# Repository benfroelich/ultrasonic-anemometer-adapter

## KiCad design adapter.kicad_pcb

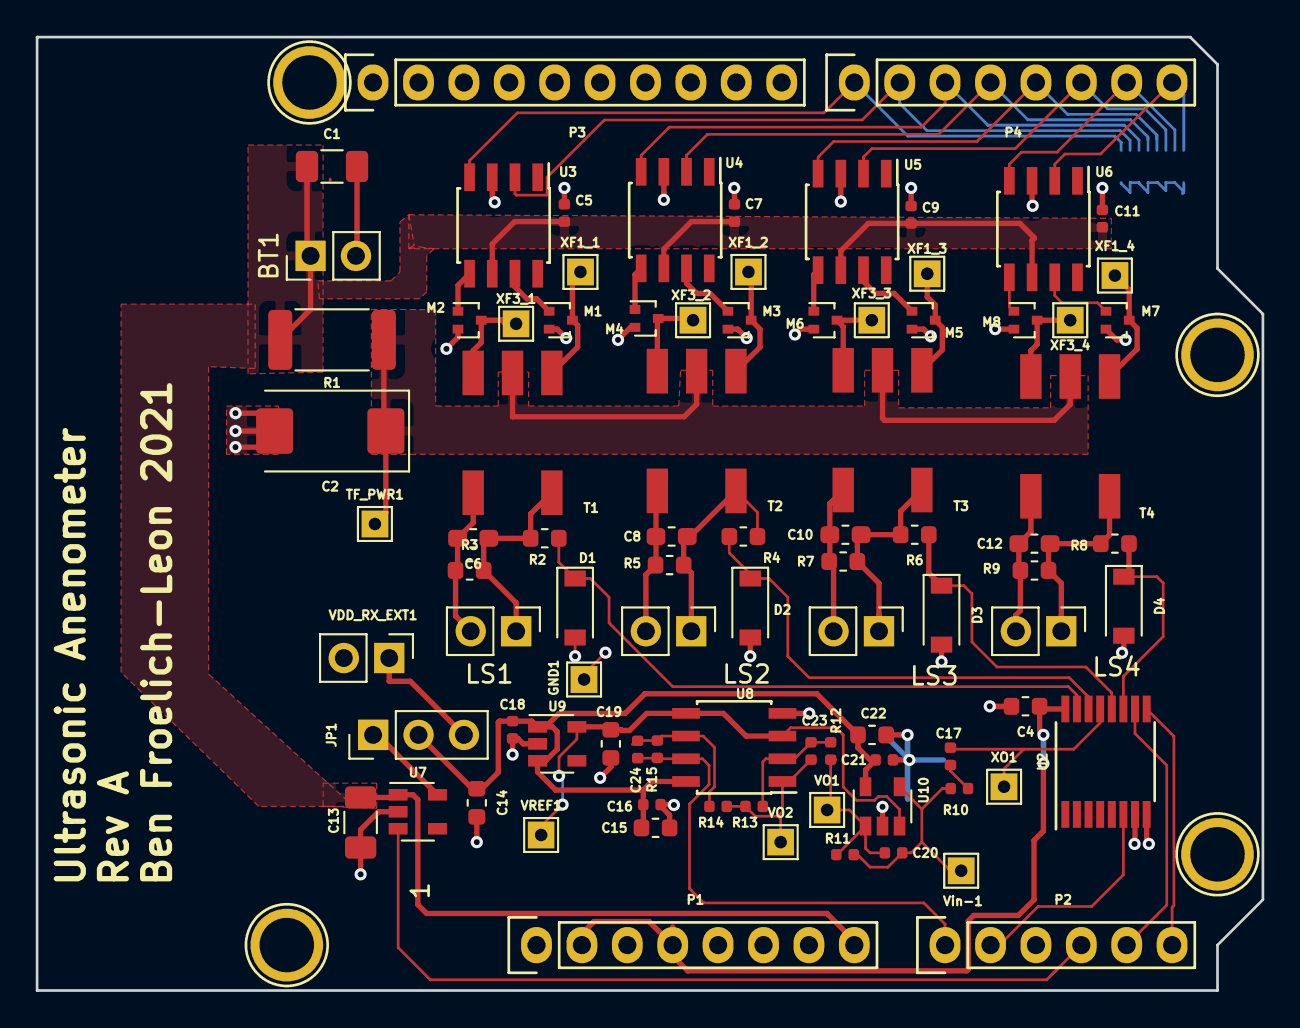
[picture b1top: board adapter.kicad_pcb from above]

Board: 2 copper layers, 68.6 x 53.3 mm, 94 parts (1 on the bottom side), 52 nets.

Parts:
BT1: 9 V; PinHeader_1x02_P2.54mm_Vertical_TE-Connectivity-640456-2‎
C1, C13: 4.7uF; C_1206_3216Metric
C2: 100uF; CP_EIA-7343-31_Kemet-D
C4: 4.7 uF; C_0603_1608Metric
C5, C7, C9, C11, C16, C18, C21: 100nF; C_0402_1005Metric
C6, C8, C10, C12: 1500p; C_0603_1608Metric_Pad1.05x0.95mm_HandSolder
C14, C15, C19, C22: 4.7uF; C_0603_1608Metric
C17: 100n; C_0402_1005Metric
C20, C23, C24: 1pF; C_0402_1005Metric
D1, D2, D3, D4: DDZ9678-7; D_SOD-123
GND1: TEST_1P; TestPoint_THTPad_1.5x1.5mm_Drill0.7mm
JP1: Jumper_3_Bridged12; PinHeader_1x03_P2.54mm_Vertical
LS1, LS2, LS3, LS4: Speaker_Ultrasound; PinHeader_1x02_P2.54mm_Vertical_TE-Connectivity-640456-2‎
M1, M2, M3, M4, M5, M6, M7, M8: PJE138K; SOT-416
P1: Power; Socket_Strip_Arduino_1x08
P2: Analog; Socket_Strip_Arduino_1x06
P3: Digital; Socket_Strip_Arduino_1x10
P4: Digital; Socket_Strip_Arduino_1x08
P5, P6, P7, P8: CONN_01X01; Arduino_1pin
R1: 100; R_2512_6332Metric
R2, R4, R6, R8: 10k; R_0603_1608Metric
R3, R5, R7, R9: 1.8k; R_0603_1608Metric
R10: 2.2k; R_0402_1005Metric
R11: 10k; R_0402_1005Metric
R12, R14: 4.3k; R_0402_1005Metric
R13, R15: 43k; R_0402_1005Metric
RN1: 100k; R_Array_Convex_8x0602
T1, T2, T3, T4: Transformer_SP_1S; B78416
TF_PWR1: TEST_1P; TestPoint_THTPad_1.5x1.5mm_Drill0.7mm
U2: SN74LV4052; TSSOP-16_4.4x5mm_P0.65mm
U3, U4, U5, U6: TC4427AVOA; SOIC-8_3.9x4.9mm_P1.27mm
U7: TPS76933; SOT-23-5
U8: OPA2322AID; SOIC-8_3.9x4.9mm_P1.27mm
U9: TLV70215_SOT23-5; SOT-23-5
U10: LMP7731MFE; SOT-23-5
VDD_RX_EXT1: TEST; PinHeader_1x02_P2.54mm_Vertical
VO1, VO2: TEST_1P; TestPoint_THTPad_1.5x1.5mm_Drill0.7mm
VREF1: TEST_1P; TestPoint_THTPad_1.5x1.5mm_Drill0.7mm
Vin-1: TEST_1P; TestPoint_THTPad_1.5x1.5mm_Drill0.7mm
XF1_1, XF1_2, XF1_3, XF1_4, XF3_1, XF3_2, XF3_3, XF3_4: TEST_1P; TestPoint_THTPad_1.5x1.5mm_Drill0.7mm
XO1: TEST_1P; TestPoint_THTPad_1.5x1.5mm_Drill0.7mm

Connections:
+3V3: C4.1, P1.2, P1.4, U2.16
+9V: BT1.1, C1.1, C5.1, C7.1, C9.1, C11.1, C13.1, P1.8, R1.2, U3.6, U4.6, U5.6, U6.6, U7.1
/PA0: C24.1, P2.1, R15.1, U8.7
/PA1: P2.2, U2.6
/PA2: P4.7, RN1.15, U6.4
/PA3: P4.8, RN1.16, U6.2
/PA8: P4.1, RN1.9, U3.4
/PA10: P4.6, RN1.14, U5.2
/PB0: P2.4, U7.3
/PB3: P4.5, RN1.13, U5.4
/PB4: P4.3, RN1.11, U4.4
/PB5: P4.4, RN1.12, U4.2
/PB10: P4.2, RN1.10, U3.2
/PC0: P2.6, U2.9
/PC1: P2.5, U2.10
/sheet618B55A2/RX: D1.1, R2.1, U2.15
/sheet618B55A3/RX: D2.1, R4.1, U2.14
/sheet618B55A4/RX: D3.1, R6.1, U2.12
/sheet618B55A5/RX: D4.1, R8.1, U2.11
/sheet618B55A6/RX_IN: C17.2, U2.13, XO1.1
/sheet618B55A6/VDD_RX: C14.1, C15.1, C16.1, C18.2, C21.1, C22.1, JP1.2, U8.8, U9.1, U9.3, U10.5
/sheet618B55A6/VDD_RX_EXT: JP1.3, VDD_RX_EXT1.1
/sheet618B55A6/v1: C20.2, R10.1, R11.2, U10.4, Vin-1.1
GND: BT1.2, C1.2, C2.2, C4.2, C5.2, C6.2, C7.2, C8.2, C9.2, C10.2, C11.2, C12.2, C13.2, C14.2, C15.2, C16.2, C18.1, C19.2, C21.2, C22.2, D1.2, D2.2, D3.2, D4.2, GND1.1, LS1.2, LS2.2, LS3.2, LS4.2, M1.2, M2.2, M3.2, M4.2, M5.2, M6.2, M7.2, M8.2, P1.6, P1.7, P3.4, R3.1, R5.1, R7.1, R9.1, RN1.1, RN1.2, RN1.3, RN1.4, RN1.5, RN1.6, RN1.7, RN1.8, T1.4, T2.4, T3.4, T4.4, U2.7, U2.8, U3.3, U4.3, U5.3, U6.3, U7.2, U8.4, U9.2, U10.2, VDD_RX_EXT1.2
unnamed: C6.1, LS1.1, R2.2, R3.2, T1.5
unnamed: C8.1, LS2.1, R4.2, R5.2, T2.5
unnamed: C10.1, LS3.1, R6.2, R7.2, T3.5
unnamed: C12.1, LS4.1, R8.2, R9.2, T4.5
unnamed: C17.1, R10.2
unnamed: C19.1, U8.3, U8.5, U9.5, U10.3, VREF1.1
unnamed: C20.1, R11.1, R12.2, U10.1, VO1.1
unnamed: C23.1, R13.1, R14.2, U8.1, VO2.1
unnamed: C23.2, R12.1, R13.2, U8.2
unnamed: C24.2, R14.1, R15.2, U8.6
unnamed: JP1.1, U7.5
unnamed: M1.1, U3.7
unnamed: M1.3, T1.1, XF1_1.1
unnamed: M2.1, U3.5
unnamed: M2.3, T1.3, XF3_1.1
unnamed: M3.1, U4.7
unnamed: M3.3, T2.1, XF1_2.1
unnamed: M4.1, U4.5
unnamed: M4.3, T2.3, XF3_2.1
unnamed: M5.1, U5.7
unnamed: M5.3, T3.1, XF1_3.1
unnamed: M6.1, U5.5
unnamed: M6.3, T3.3, XF3_3.1
unnamed: M7.1, U6.7
unnamed: M7.3, T4.1, XF1_4.1
unnamed: M8.1, U6.5
unnamed: M8.3, T4.3, XF3_4.1
TF_PWR: C2.1, R1.1, T1.2, T2.2, T3.2, T4.2, TF_PWR1.1

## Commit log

2021-12-07 initial commit, initial PCB rev sent to OSH Park
